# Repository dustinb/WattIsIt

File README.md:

# Camp Sense

Camp Sense connects to WattIsIt via bluetooth and displays the energy and weather data. The `App` folder contains
the React Native app developed using Expo.

|                     Energy                     |                    Weather                    |
| :--------------------------------------------: | :-------------------------------------------: |
|  |  |

# WattIsIT

A battery watt meter using ADS1115 and a shunt to measure power usage. There are 2 Arduino sketches, `Arduino/RemoteXY` and `Arduino/Camp Sense`. The latter uses Platform IO plugin for VSCode and works with the Camp Sense app.

## BOM

AHT21 is optional, was used for humidity but also has a temperature sensor.

| Item           | Link                   |
| -------------- | ---------------------- |
| U2 ESP32       | https://a.co/d/88cG9Z5 |
| M1 ADS1115     | https://a.co/d/gfCO6jt |
| U1 Voltage Reg | https://a.co/d/cpmFpuU |
| U4 AHT21       | https://a.co/d/6xBWBLx |
| U3 BMP280      | https://a.co/d/1HV9oyw |
| J1 Terminals   | https://a.co/d/8nVocXb |
| Shunt          | https://a.co/d/7QWWK5O |
| R1 10k Ohm     | https://a.co/d/6f4wvqz |
| R2 5k Ohm      | https://a.co/d/adCeki6 |

## Version 1.0

|                KiCad Model                |                 In Use                  |
| :---------------------------------------: | :-------------------------------------: |
|  |  |

## Screw Connections

\+ 12 volt + \
\- 12 volt - \
L Low side of shunt \
H High side of shunt

## Remote XY

Before the Camp Sense app Remote XY was used for development. The sketch is in `Arduino/RemoteXY`.

The Remote XY is a free app is used to view data with bluetooh. This also has a setting for the shunt 50, 75, or 100 mV. The setting is persisted in eeprom (flash memory)

https://remotexy.com/en/editor/391325040dffc13fc4e74f019a2b24ee/

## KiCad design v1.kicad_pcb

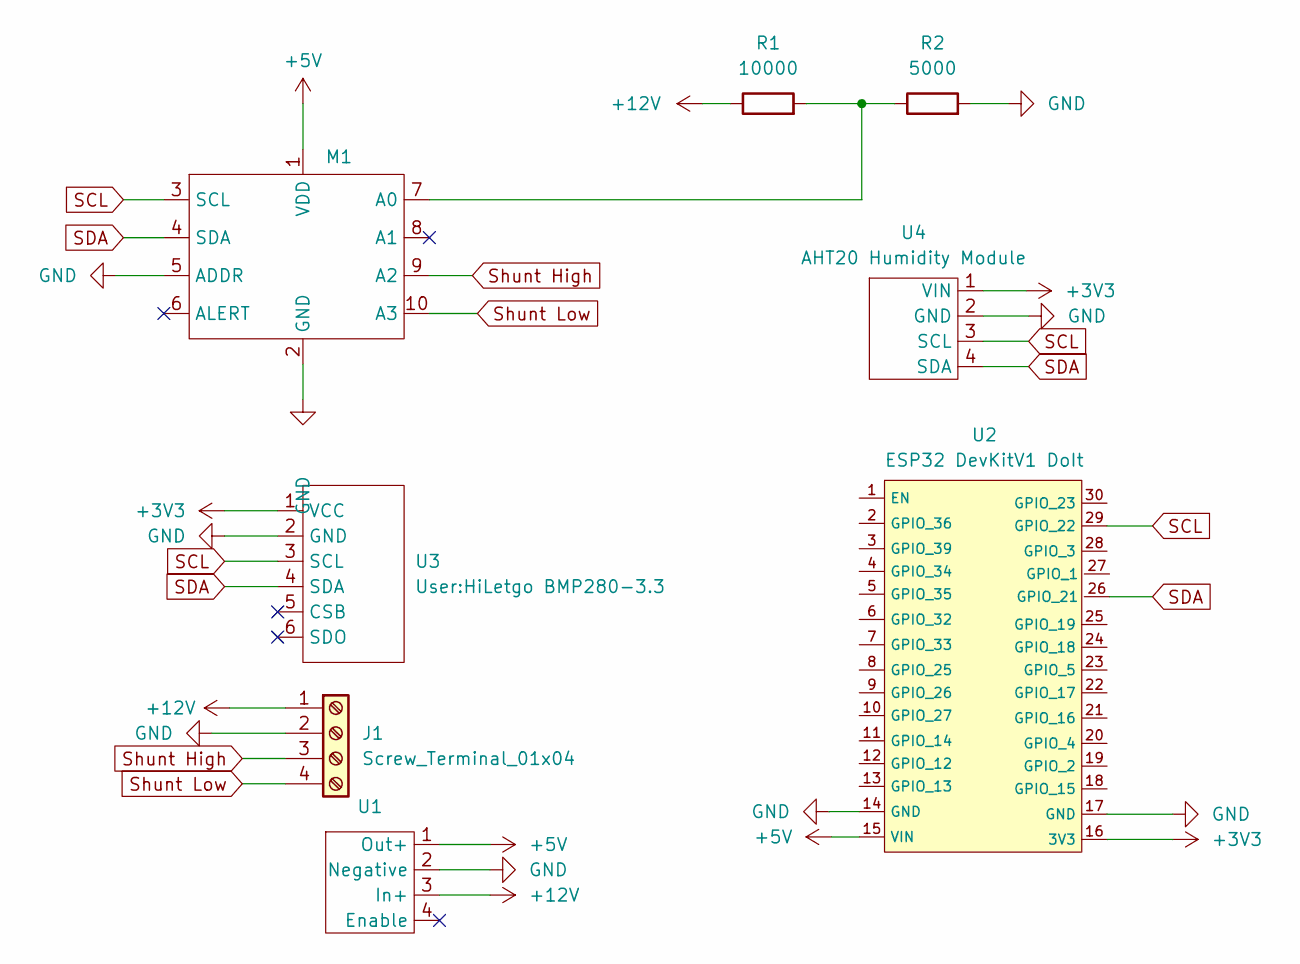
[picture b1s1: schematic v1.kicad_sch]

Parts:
J1: Screw_Terminal_01x04; Screw Terminal 2.54 x4
M1: ADS1115
R1: 10000; R_Axial_DIN0207_L6.3mm_D2.5mm_P10.16mm_Horizontal
R2: 5000; R_Axial_DIN0207_L6.3mm_D2.5mm_P10.16mm_Horizontal
U1: Drok Vreg
U2: ESP32 DevKitV1 DoIt
U3: HiLetgo BMP280-3.3
U4: AHT20 Humidity Module

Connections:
+3V3: U2.16 (3V3), U3.1 (VCC), U4.1 (VIN)
+5V: M1.1 (VDD), U1.1 (Out+), U2.15 (VIN)
+12V: J1.1, R1.1, U1.3 (In+)
GND: J1.2, M1.2 (GND), M1.5 (ADDR), R2.2, U1.2 (Negative), U2.14 (GND), U2.17 (GND), U3.2 (GND), U4.2 (GND)
unnamed: M1.7 (A0), R1.2, R2.1
SCL: M1.3 (SCL), U2.29 (GPIO_22), U3.3 (SCL), U4.3 (SCL)
SDA: M1.4 (SDA), U2.26 (GPIO_21), U3.4 (SDA), U4.4 (SDA)
Shunt High: J1.3, M1.9 (A2)
Shunt Low: J1.4, M1.10 (A3)

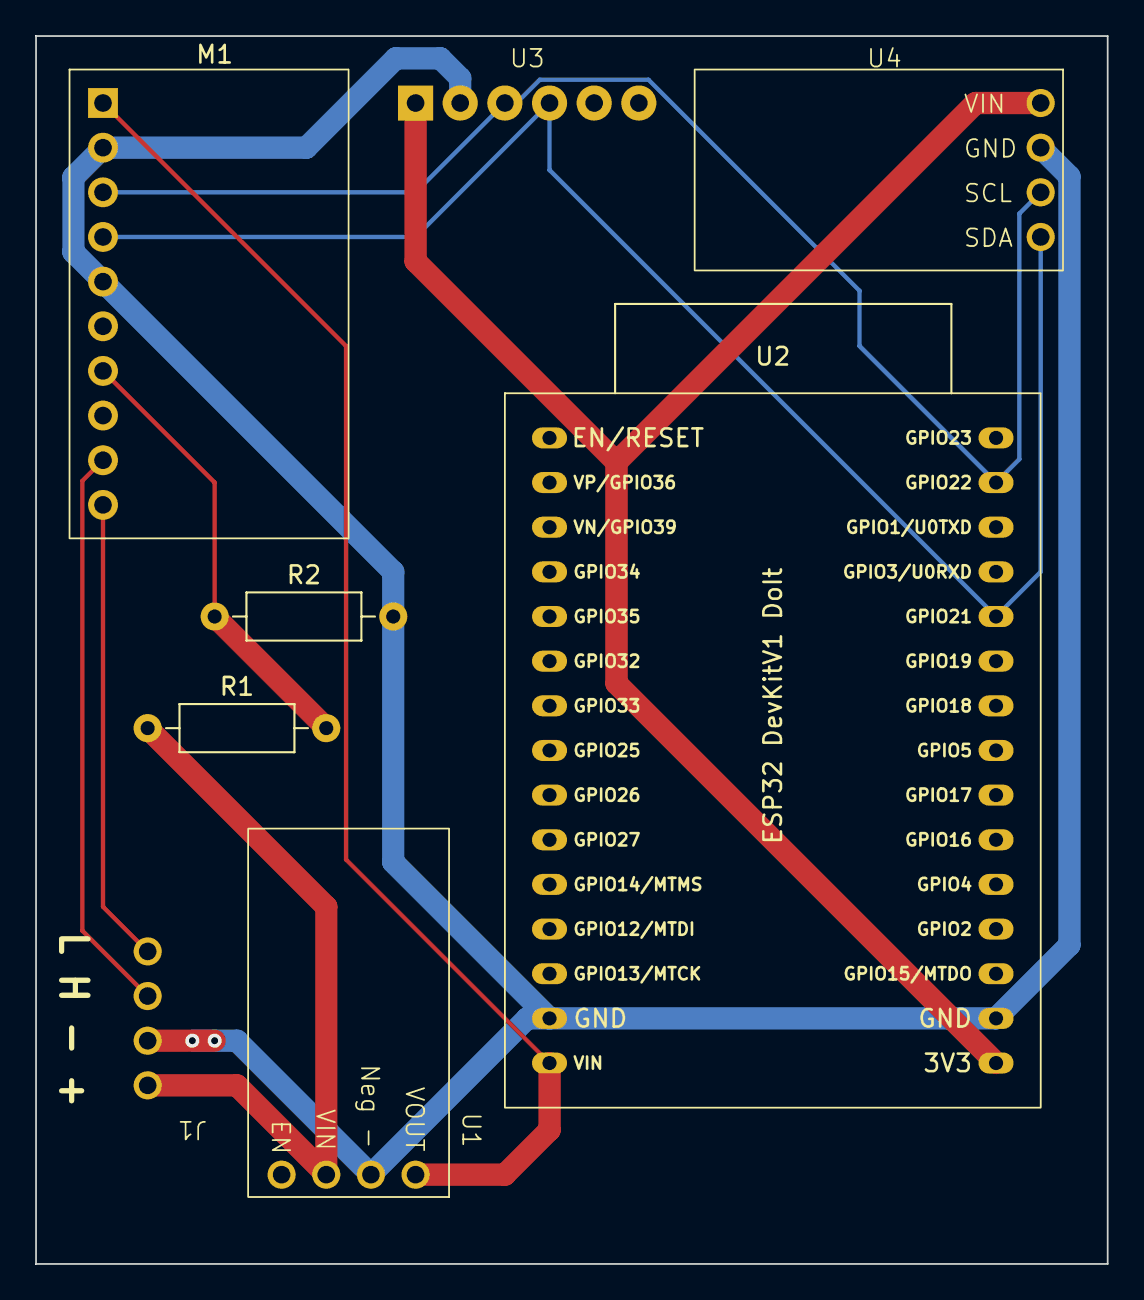
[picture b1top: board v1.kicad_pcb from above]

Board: 2 copper layers, 61.0 x 69.8 mm, 8 parts (0 on the bottom side), 9 nets.

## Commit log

2023-11-17 Init version 1.0
2024-06-09 Camp Sense v1. WattIsIt ble sketch
